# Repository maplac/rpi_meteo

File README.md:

# rpi_meteo

Installation (incomplete)

Install Influx and Grafana.
https://simonhearne.com/2020/pi-influx-grafana/
"sudo apt install influxdb-client" if command influx doesn't work.

Add cron jobs.
$ crontab -e
* * * * * python3 /home/pi/rpi_meteo/python/bme280_reader.py >/dev/null 2>&1
# old driver for I2C 20x4 LCD display (not used enymore)
#* * * * * python3 /home/pi/rpi_meteo/python/lcd_driver.py >/dev/null 2>&1

Make sure the pigpiod service is enabled and running (required by rf24_receiver).
$ systemctl status pigpiod

Make the 'brightness' file editable by non-root user (required by backlight_driver).
sudo touch /etc/udev/rules.d/backlight-permissions.rules
sudo echo "SUBSYSTEM==\"backlight\",RUN+=\"/bin/chmod 666 /sys/class/backlight/%k/brightness /sys/class/backlight/%k/bl_power\"" > /etc/udev/rules.d/backlight-permissions.rules

Install service.
sudo cp /home/pi/rpi_meteo/python/rf24_receiver.service /lib/systemd/system/rf24_receiver.service
sudo systemctl start rf24_receiver
sudo systemctl enable rf24_receiver

sudo cp /home/pi/rpi_meteo/python/backlight_driver.service /lib/systemd/system/backlight_driver.service
sudo systemctl start backlight_driver
sudo systemctl enable backlight_driver

Install 'unclutter' to hide mouse cursor.
sudo apt install unclutter

Starting Grafana in web browser automatically after boot

Install Firefox (Chromium stopped working on my Rpi) $sudo apt-get install firefox-esr
Install ForceFull addon in Firefox. The addon automatically switches the Firefox to fullscreen mode.

Doesn't work:
Add following lines to file /home/pi/.config/lxsession/LXDE-pi/autostart
@lxpanel --profile LXDE-pi
@pcmanfm --desktop --profile LXDE-pi
#@xscreensaver -no-splash
point-rpi
@unclutter -idle 0
@firefox -url  http://localhost:3000/d/uZDC-7zgk/rpi_meteo-testing-simple?orgId=1&refresh=1m&kiosk
Do work:
Use firefox_starter.service or start_firefox_with_delay, one of them probably works.
Append "@unclutter -idle 0" to /etc/xdg/lxsession/LXDE-pi/autostart.

Modify InfluxDB settings to reduce CPU and RAM usage.
[data]
cache-max-memory-size = "512m"
max-concurrent-compactions = 2
[monitor]
store-enabled = false
From https://github.com/nikobockerman/ruuvitags-raspberrypi/tree/master/influxdb#initial-creation

Stop and disable telegraf.
systemctl disable telegraf

Grafana
Install Clock plugin.
sudo grafana-cli plugins install grafana-clock-panel
sudo systemctl restart grafana-server
Configure datasources

Arduino UNO project in test folder is based on https://github.com/bjarne-hansen/py-nrf24/blob/master/arduino/simple-sender/simple-sender.ino
Testing Python script rf24_receiver_01.py is based on https://github.com/bjarne-hansen/py-nrf24/blob/master/test/int-receiver.py

usermod -a - G gpio pi
usermod -a - G dialout pi
usermod -a - G i2c pi
Enable i2c and serial in "raspi-config".

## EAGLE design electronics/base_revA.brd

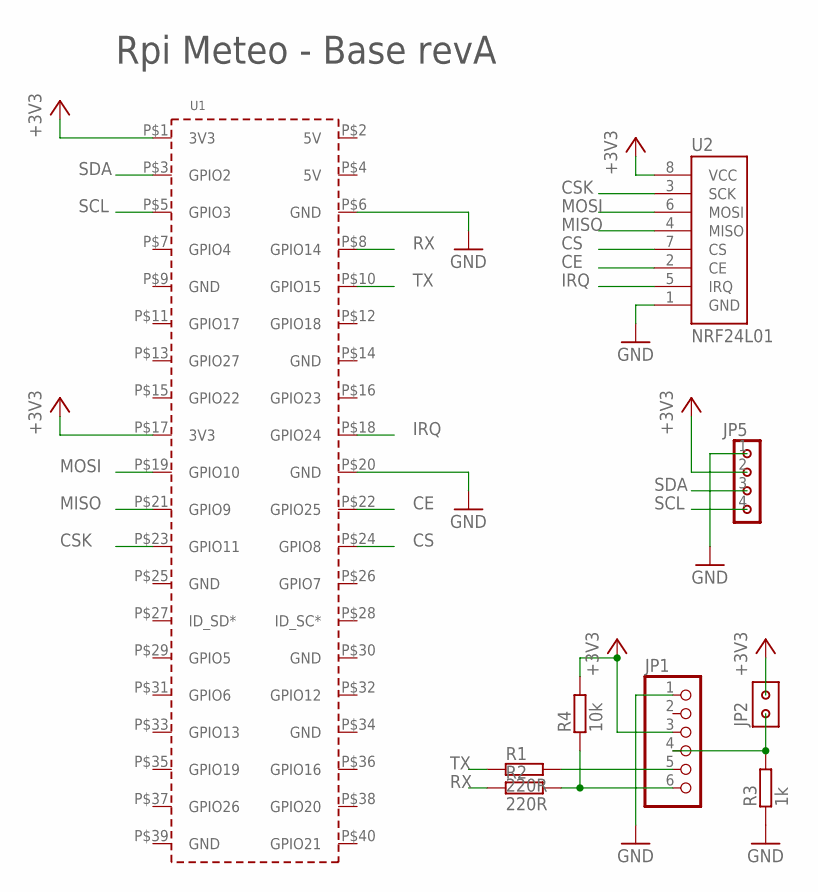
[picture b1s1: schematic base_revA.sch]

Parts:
JP1: PINHD-1X6; 1X06
JP2: PINHD-2X1
JP5: PINHD-4X1'BASIC'; 1X04
R1, R2: 220R; 0207-10
R3: 1k; 0207-10
R4: 10k; 0207-10
U1: RPI3_SIMPLE'FULL'; RPI3
U2: NRF24L01

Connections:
+3V3: JP1.3, JP2.1, JP5.2, R4.2, U1.P$1 (3V3), U1.P$17 (3V3), U2.8 (VCC)
CE: U1.P$22 (GPIO25), U2.2 (CE)
CS: U1.P$24 (GPIO8), U2.7 (CS)
CSK: U1.P$23 (GPIO11), U2.3 (SCK)
GND: JP1.1, JP5.1, R3.1, U1.P$6 (GND), U1.P$20 (GND), U2.1 (GND)
IRQ: U1.P$18 (GPIO24), U2.5 (IRQ)
MISO: U1.P$21 (GPIO9), U2.4 (MISO)
MOSI: U1.P$19 (GPIO10), U2.6 (MOSI)
unnamed: JP1.4, JP2.2, R3.2
unnamed: JP1.6, R2.2, R4.1
unnamed: JP1.5, R1.2
RX: R2.1, U1.P$8 (GPIO14)
SCL: JP5.4, U1.P$5 (GPIO3)
SDA: JP5.3, U1.P$3 (GPIO2)
TX: R1.1, U1.P$10 (GPIO15)

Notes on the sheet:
Rpi Meteo - Base revA

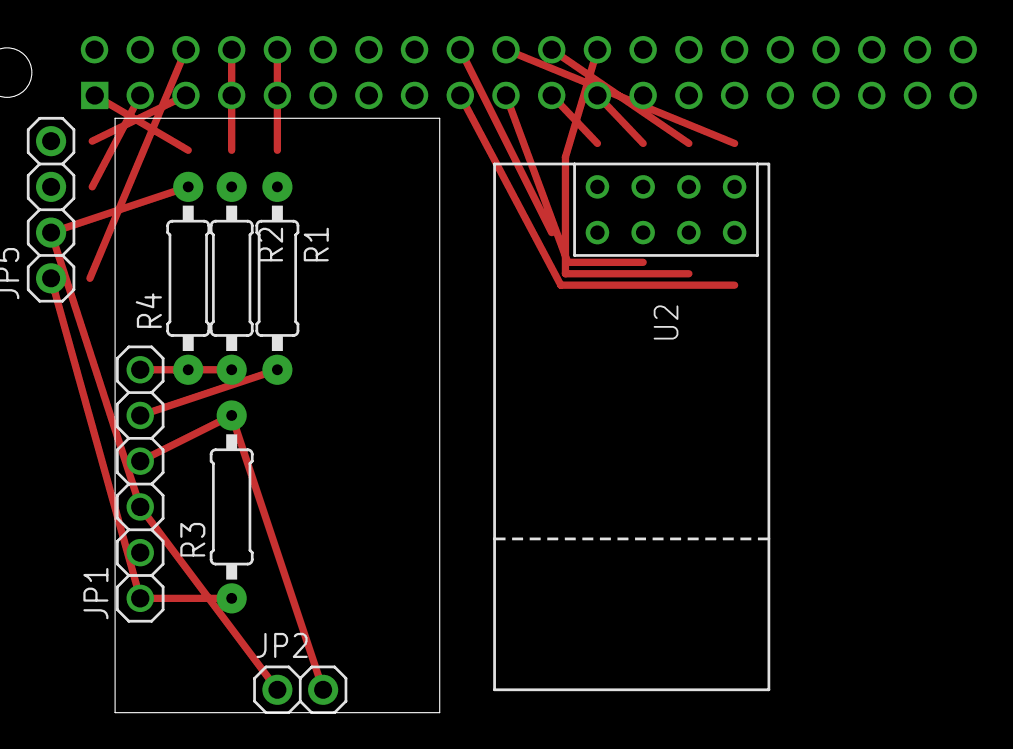
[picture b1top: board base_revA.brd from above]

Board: 2 copper layers, 9 parts (0 on the bottom side), 15 nets.

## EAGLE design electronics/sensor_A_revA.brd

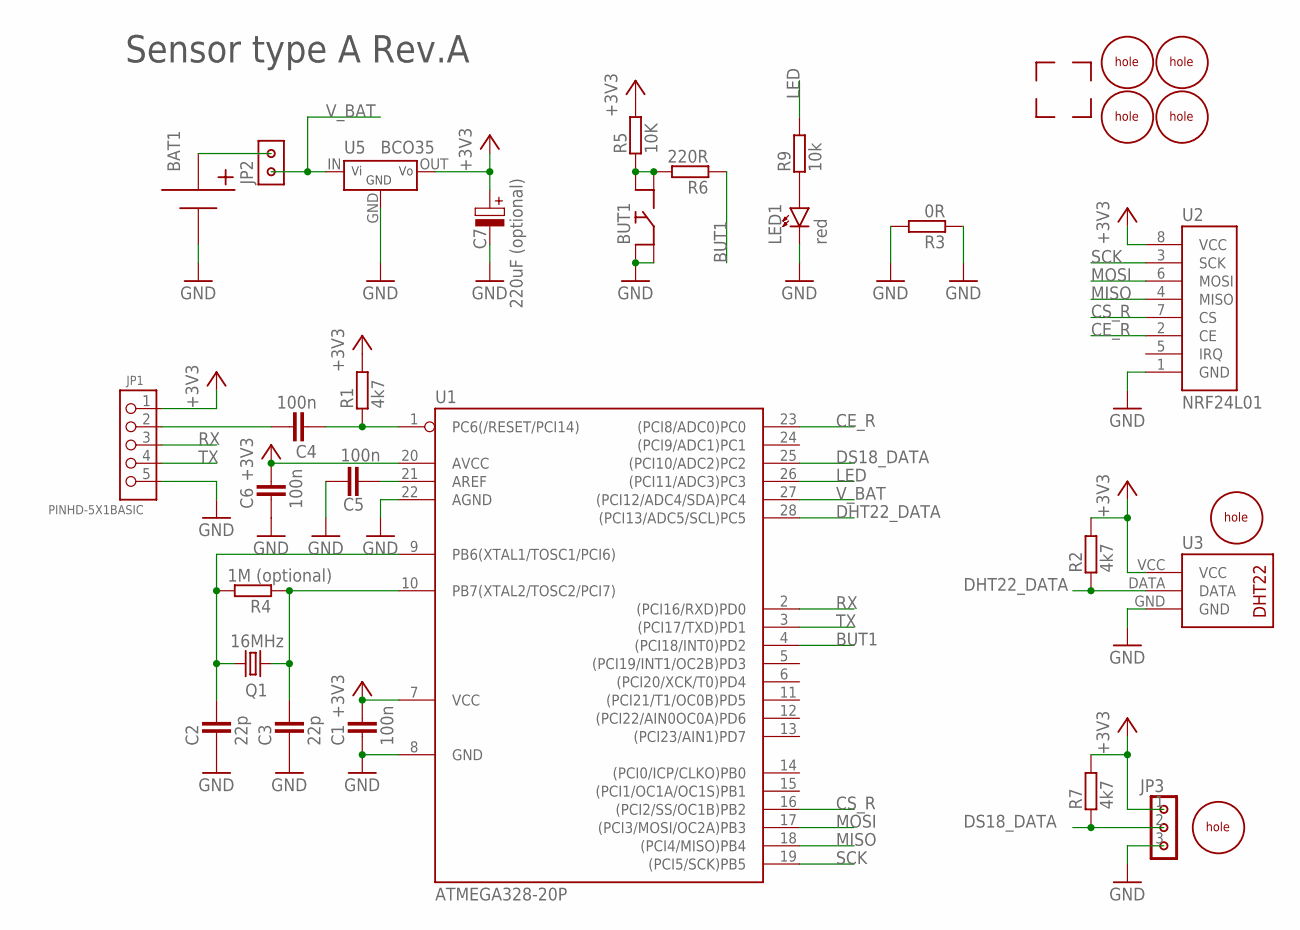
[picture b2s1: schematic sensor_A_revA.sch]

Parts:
BAT1: BATTERY_1X2X1XAAA; 1XAA_BATTERY_HOLDER_DOUBLE
BUT1: BUTTON'THT'; BUTTON
C1, C4, C5, C6: 100n; C0805
C2, C3: 22p; C0805
C7: 220uF (optional); ELYT-6MM5
JP1: PINHD-5X1BASIC; PINHD-5X1
JP2: PINHD-2X1
JP3: PINHD-3X1
LED1: red; LED5MM
Q1: 16MHz; HC49/S
R1, R2, R7: 4k7; R0805
R3: 0R; R0805
R4: 1M (optional); R0805
R5: 10K; R0805
R6: 220R; R0805
R9: 10k; R0805
U1: ATMEGA328-20P; DIL28-3
U2: NRF24L01
U3: DHT2290; DHT22/90
U5: BCO35
U$1, U$2, U$3, U$4: CORNER
U$5, U$6, U$7, U$8, U$9, U$10: HOLE

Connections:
+3V3: C1.2, C6.2, C7.+ (POS), JP1.1, JP3.1, R1.2, R2.2, R5.2, R7.2, U1.7 (VCC), U1.20 (AVCC), U2.8 (VCC), U3.VCC, U5.OUT (VOUT)
BUT1: R6.1, U1.4 ((PCI18/INT0)PD2)
CE_R: U1.23 ((PCI8/ADC0)PC0), U2.2 (CE)
CS_R: U1.16 ((PCI2/SS/OC1B)PB2), U2.7 (CS)
DHT22_DATA: R2.1, U1.28 ((PCI13/ADC5/SCL)PC5), U3.DATA
DS18_DATA: JP3.2, R7.1, U1.25 ((PCI10/ADC2)PC2)
GND: BAT1.N, BAT1.N1 (N), BUT1.2, BUT1.4, C1.1, C2.1, C3.1, C5.2, C6.1, C7.- (NEG), JP1.5, JP3.3, LED1.K, R3.1, R3.2, U1.8 (GND), U1.22 (AGND), U2.1 (GND), U3.GND, U5.GND
LED: R9.2, U1.26 ((PCI11/ADC3)PC3)
MISO: U1.18 ((PCI4/MISO)PB4), U2.4 (MISO)
MOSI: U1.17 ((PCI3/MOSI/OC2A)PB3), U2.6 (MOSI)
unnamed: C3.2, Q1.1, R4.1, U1.10 (PB7(XTAL2/TOSC2/PCI7))
unnamed: C4.1, R1.1, U1.1 (PC6(/RESET/PCI14))
unnamed: C2.2, Q1.2, R4.2, U1.9 (PB6(XTAL1/TOSC1/PCI6))
unnamed: C5.1, U1.21 (AREF)
unnamed: C4.2, JP1.2
unnamed: BAT1.P, BAT1.P1, JP2.1
unnamed: BUT1.1, BUT1.3, R5.1, R6.2
unnamed: LED1.A, R9.1
RX: JP1.3, U1.2 ((PCI16/RXD)PD0)
SCK: U1.19 ((PCI5/SCK)PB5), U2.3 (SCK)
TX: JP1.4, U1.3 ((PCI17/TXD)PD1)
V_BAT: JP2.2, U1.27 ((PCI12/ADC4/SDA)PC4), U5.IN (VIN)

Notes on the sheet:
Sensor type A Rev.A

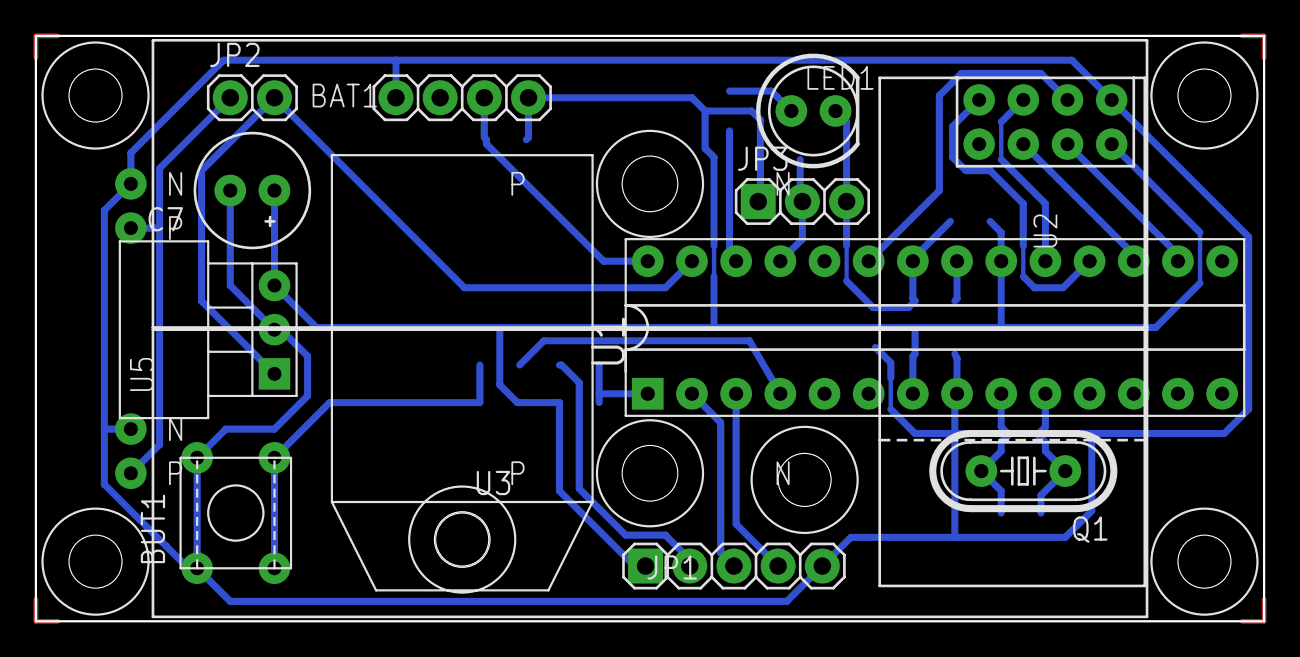
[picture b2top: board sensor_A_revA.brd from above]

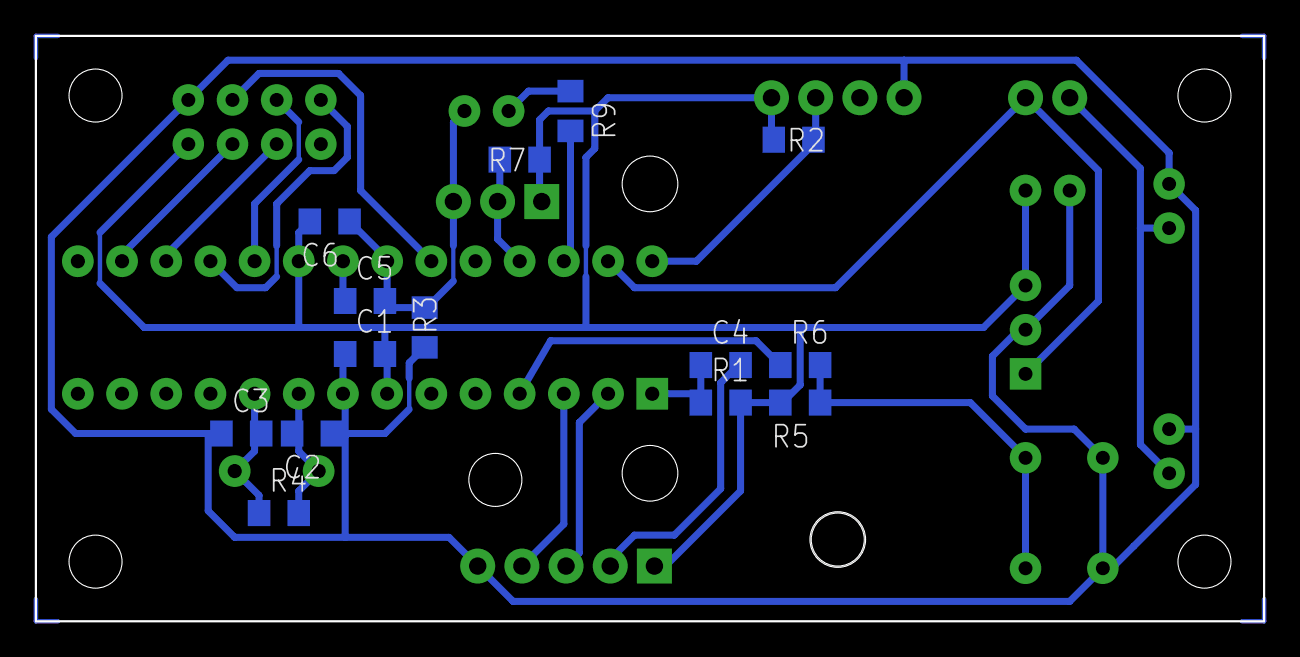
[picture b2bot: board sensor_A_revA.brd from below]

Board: 2 copper layers, 70.6 x 33.7 mm, 36 parts (14 on the bottom side), 22 nets.

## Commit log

2022-05-05 added test project for Arduino UNO
2022-05-05 Created README.md file.
2022-05-10 added testing RF24 receiver
2022-05-18 added BME280 reader
2022-05-18 modified Arduino test
2022-05-18 added LCD driver
2022-05-23 added firmware for LCD backlight driver
2022-05-31 added firmware for sensor type A
2022-06-19 modified FW for sensor A
2022-06-19 added RF24 receiver for remote sensors
2022-06-19 LCD driver shows values from remote sensors
2022-07-22 modified FW for sensor A - added support for DS18B20
2022-07-23 added installation instructions
2022-07-23 RF24 receiver can process DS18B20 temperature from sensor A
2022-07-24 added PCB for sensor A
2022-07-26 added firmware that forwards data from RF24 to UART
2022-07-26 added script that receives data from UART
2022-07-31 added testing script for reading pin status
2022-07-31 modified pin interrupt in RF24 receiver
2022-08-07 modified FW for LCD backlight driver
2022-08-07 added service for automatic backlight adjustment
2022-08-13 added: PCB for base board that is mounted on the Rpi
2022-08-13 minor adjustments in some scripts
2022-08-13 InfluxDB measurement changed from test to rpi_meteo
2022-08-13 added Grafana dashboard
2022-08-13 added images of the finished project
2022-08-13 added installation instruction
2024-02-25 migration to Raspberry Pi 4
